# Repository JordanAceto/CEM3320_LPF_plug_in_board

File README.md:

# NOTE: development of all VCF plug-in boards has been moved here https://github.com/JordanAceto/VCF_plug_in_boards
### This repo will no longer be updated. Follow the above link for the most current files.

# CEM3320 Plug-In Board

Small CEM3320 based low pass filter PCB, designed to plug into a larger motherboard.

## Details

CEM3320 based LPF with Q compensation. This PCB includes the audio path and CV inputs for frequency and feedback, but does not include any modulation sources.

The intended use for this board is to plug in to a larger motherboard which contains slots for two of these plug-in boards, as well as modulation sources, panel controls, and input/output routing. This motherboard could accept different filter boards sharing this footprint and header layout, for realizing stereo effects of various flavors.

The Q compensation circuit keeps the passband gain from dropping too much when feedback is increased as typically happens with this type of filter. This is a matter of taste. The amount of compensation is set by R20. R20 can be increased to reduce the amount of compensation, resulting in lower passband gain at high feedback settings if a more traditional response is desired.

## Inputs

-Audio in: dry audio input to be filtered.

-Frequency CV in: 0 volts to +2.048 volts, higher voltage = higher sweep.

-Feedback CV in: 0 volts to +2.048 volts, higher voltage = more feedback.

## Outputs

-Audio out: filtered audio output.

## Power Supply Requirements

A bipolar 12 volt power supply is required. This will typically come from the motherboard.

## Calibration

-RV1 (depth trim): trims the depth of incoming frequency CV signals. Turn CW for greater depth and CCW for less depth. Adjust to taste.

-RV2 (center trim): trims the center frequency of the filter. Turn CW for higher center frequency and CCW for lower center frequency. Adjust to taste.

-RV3 (feedback trim): trims the maximum amount of feedback. Turn CW for more maximum feedback and CCW for less maximum feedback. Exercise caution when adjusting this, as extreme settings can result in loud oscillations which could damage your ears or speakers if you are monitoring the sound with a loud amplifier. If you set this trimmer to be right on the edge of oscillation when about +2 volts is applied to the feedback CV input then make sure to sweep the frequency through its entire range, as a setting that doesn't squeal at certain frequency settings may squeal at other settings.

## Parts Ordering
The BOM has a link to a Mouser project with the majority of the parts needed to build the board, with the exception of the CEM3320. There is a link to the synthcube parts page, where the AS3320 is available. This is a functionally equivalent part that is currently in production.

Gerbers can be generated from the kicad_docs.

## License
CC by 4.0

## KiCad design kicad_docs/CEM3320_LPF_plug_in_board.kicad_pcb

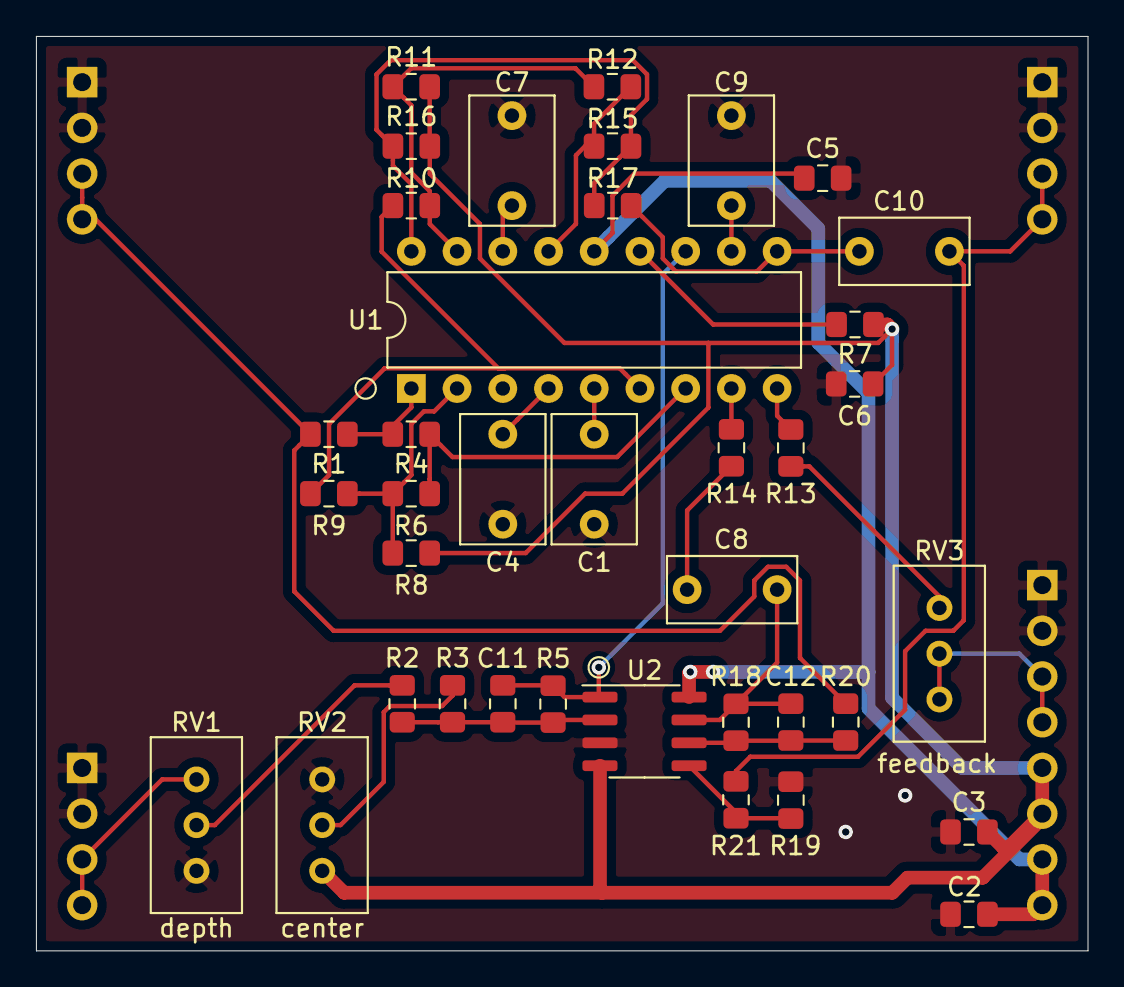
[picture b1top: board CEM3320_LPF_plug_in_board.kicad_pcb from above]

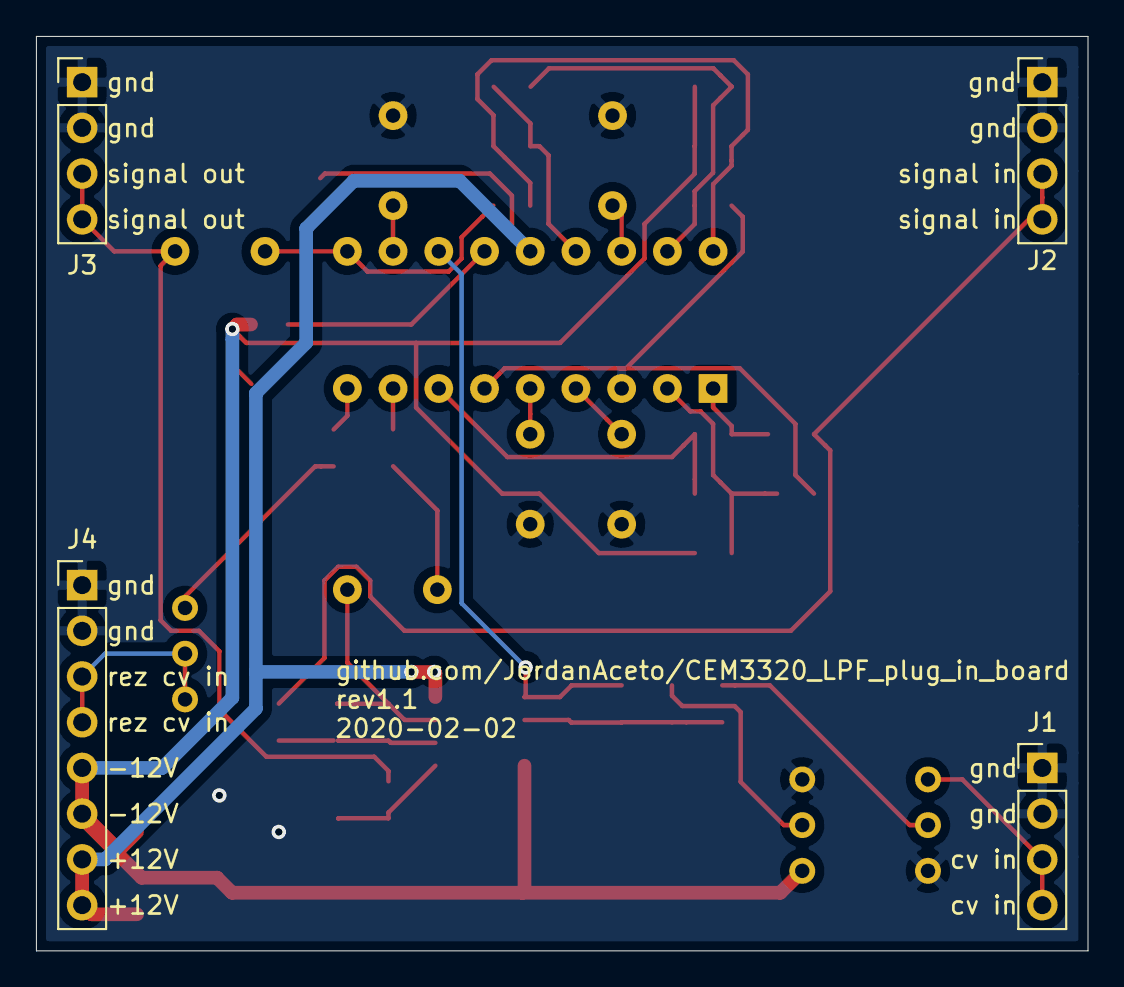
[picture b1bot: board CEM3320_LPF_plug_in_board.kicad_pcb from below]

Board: 2 copper layers, 58.4 x 50.8 mm, 42 parts (4 on the bottom side), 31 nets.

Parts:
C1, C4, C7, C9: 220pF; C_Rect_L7.0mm_W4.5mm_P5.00mm
C2, C3, C5, C6: 100nF; C_0805_2012Metric_Pad1.15x1.40mm_HandSolder
C8, C10: 470nF; C_Rect_L7.0mm_W3.5mm_P5.00mm
C11, C12: 100pF; C_0805_2012Metric_Pad1.15x1.40mm_HandSolder
J1, J2: signal_in; PinHeader_1x04_P2.54mm_Vertical
J3: signal_out; PinHeader_1x04_P2.54mm_Vertical
J4: Conn_01x08_Male; PinHeader_1x08_P2.54mm_Vertical
R1, R6, R10, R15: 91k; R_0805_2012Metric_Pad1.15x1.40mm_HandSolder
R2, R4, R9, R12, R17, R18, R19, R21: 100k; R_0805_2012Metric_Pad1.15x1.40mm_HandSolder
R3: 330k; R_0805_2012Metric_Pad1.15x1.40mm_HandSolder
R5: 10k; R_0805_2012Metric_Pad1.15x1.40mm_HandSolder
R7: 1k2; R_0805_2012Metric_Pad1.15x1.40mm_HandSolder
R8, R11, R16: 180k; R_0805_2012Metric_Pad1.15x1.40mm_HandSolder
R13: 18k; R_0805_2012Metric_Pad1.15x1.40mm_HandSolder
R14: 51k; R_0805_2012Metric_Pad1.15x1.40mm_HandSolder
R20: 150k; R_0805_2012Metric_Pad1.15x1.40mm_HandSolder
RV1: 10k; Potentiometer_Bourns_3296W_Vertical
RV2, RV3: 100k; Potentiometer_Bourns_3296W_Vertical
U1: CEM3320; DIP-18_W7.62mm
U2: TL072; SOIC-8_3.9x4.9mm_P1.27mm

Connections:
+12V: C2.1, C5.1, J4.7, J4.8, U1.14, U2.8
-12V: C3.2, C6.2, J4.5, J4.6, R7.1, R8.2, R11.2, R16.2, RV2.1, U2.4
/dry: J2.3, J2.4, R1.2, R20.1
/wet: C10.1, J3.3, J3.4, R21.2
GND: C1.2, C2.2, C3.1, C4.2, C5.2, C6.1, C7.2, C9.2, J1.1, J1.2, J2.1, J2.2, J3.1, J3.2, J4.1, J4.2, R19.2, RV1.1, RV2.3, U1.3, U2.3
unnamed: C1.1, U1.5
unnamed: C4.1, U1.4
unnamed: C7.1, U1.16
unnamed: C8.2, R14.1
unnamed: C9.1, U1.11
unnamed: C10.2, R17.1, U1.10
unnamed: C11.1, R2.1, R3.2, R5.2, U2.2
unnamed: C11.2, R5.1, U1.12, U2.1
unnamed: C8.1, C12.1, R18.1, U2.7
unnamed: C12.2, R18.2, R20.2, U2.6
unnamed: J1.3, J1.4, RV1.3
unnamed: J4.3, J4.4, RV3.1, RV3.2
unnamed: R1.1, R4.2, U1.1
unnamed: R2.2, RV1.2
unnamed: R3.1, RV2.2
unnamed: R4.1, R6.2, U1.7
unnamed: R6.1, R8.1, R9.2, U1.2
unnamed: R7.2, U1.13
unnamed: R10.1, R11.1, R12.2, U1.17
unnamed: R9.1, R10.2, U1.6
unnamed: R12.1, R15.2, U1.15
unnamed: R13.1, U1.9
unnamed: R13.2, RV3.3
unnamed: R14.2, U1.8
unnamed: R15.1, R16.1, R17.2, U1.18
unnamed: R19.1, R21.1, U2.5

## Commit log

2019-06-09 add rendered pics of board top and bottom
2019-06-09 add README.md
2019-06-09 edit README, add note about Q compensation
2019-06-11 add gerbers
2019-06-11 update README to include zipped gerbers
2019-06-18 fix silkscreen issue where R8 and R6 refs overlapped
2019-06-18 add link to oshpark
2019-06-18 fix typo in README
2019-07-12 fix reversed power pins on TL072 in schm and brd, delete bad gerbers
2019-07-12 fix reversed power pins on TL072 in shem pdf
2020-02-02 change trimmers to cheaper though hole type
2020-02-02 update pcb silkscreen
2020-02-02 update readme with new pics, remove mention of OSHpark
2020-02-02 update pics
2020-02-02 Create LICENSE
2020-08-01 update readme to link to new repo
